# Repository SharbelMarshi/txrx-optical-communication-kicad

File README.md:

# A Free Space Optical Communication
This project implements a free-space optical communication link using two separate KiCad-designed boards: a transmitter and a receiver. The transmitter uses an RP2354A microcontroller to frame arbitrary digital payloads into packets and generate $100 \mathrm{kbit/s}$ RZ-OOK modulation for a $650 \mathrm{nm}$ laser module through a level-shifting buffer and an independent hardware safety chain.
The receiver uses a BPW34 photodiode, OPA320 transimpedance amplifier, and TLV3201 comparator (with an adaptive, average-tracking threshold and hysteresis) to recover the optical pulses and feed them into an RP2354A for decoding, CRC verification, and delivery to the host system.
Both boards include USB-C, UART, SWD, a local $12 \mathrm{MHz}$ crystal, and a $10 \mathrm{MHz}$ SiTime SiT5346 DCTCXO reference. The SiT5346 is connected to the RP2354A through a GPIO/PIO clock input and is controllable over the existing $\text{I²C}$ bus. Each board also exposes a dedicated $1\mathrm{PPS}$ output generated by the RP2354A. The initial target is a stable free-space optical link over approximately $5$ meters.

## Architecture
Two separate $4$ layer boards:
- TX: RP2354A + USB-C + host I/O + $12 \mathrm{MHz}$ crystal + $10 \mathrm{MHz}$ SiT5346 DCTCXO + dedicated $1\mathrm{PPS}$ output + laser driver/safety chain + laser module + power LED + host-5 V TVS protection.
- RX: RP2354A + USB-C + host I/O + $12 \mathrm{MHz}$ crystal + $10 \mathrm{MHz}$ SiT5346 DCTCXO + dedicated $1\mathrm{PPS}$ output + BPW34 / OPA320 / TLV3201 optical receiver + ADC monitor + power LED + host-5 V TVS protection.

### TX
- TX_ROOT
- TX_POWER_USB
- TX_MCU_CLOCK
- TX_HOST_IO
- TX_LASER

### RX
- RX_ROOT
- RX_POWER_USB
- RX_MCU_CLOCK
- RX_HOST_IO
- RX_OPTICAL_AFE
- RX_MONITOR

### TX schamtics:

### TX PCB: 

### RX schamtics:

### RX PCB: 

## Design updates (November 2026)
- **JLCPCB stock swaps:** 12 MHz crystal → YXC X322512MMB4SI; laser arm switch SW3 → C&K JS202011CQN; J2 / TX J4 → Würth 2.54 mm headers; USB-C → HH 16P TYPE-C (Y495); SWD header → FTSH-105-01-F-DV-K.
- **RX optical front end:** TIA gain R15 = 10 kΩ with C28 = 10 pF; adaptive comparator threshold (R13 = 100 kΩ from TIA_OUT, R12 = 2.2 MΩ, C25 = 10 nF); hysteresis via R16 = 1 kΩ and R17 = 470 kΩ.
- **Protection and indicators:** host 5 V input TVS (TX D2 SMF5.0A, RX D3 CESD5V0D3); red power LED on +3V3_DIG (TX R15/D1, RX R19/D2); 10 µF bulk capacitor on the TX 5 V rail (C26).
- **10 MHz reference:** 33 Ω series source termination at each SiT5346 output (TX R14, RX R18; oscillator side net `REF_10M_SRC`).
- **Decoupling:** two extra 100 nF 0402 capacitors on RX (C30 at IOVDD pin 45, C31 at VREG_VIN pin 49). The RP2354A core-supply (DVDD) decoupling still needs a manual fan-out rework, since there is no room near those pins without rerouting.
- **Test points:** RX TP1 = TIA_OUT, TP2 = COMP_THRESHOLD (bottom side), TP3 = RX_DATA_DIG; TX TP1 = LASER_DATA_3V3. Laser power/data and GND are also on the TX J4 header pins.
- **Silkscreen:** bottom-side pin names for J2, JP1 (USB / HOST), J4, J5/J6, test points, and board name/revision. SW3 is marked **ARM** (slider toward the top end, pin 1) and **SAFE**, per the C&K JS circuit diagram; confirm with a meter before first laser use.
- **Panelization:** copper-to-edge clearance raised to 0.4 mm for V-scoring. The RX outline was widened by 2.5 mm on the left (header side, no copper), so both boards are 52.09 × 40.0 mm and V-score lines line up. Panel options (all 2×2, V-scored, 5 mm rails with tooling holes and fiducials):
  - `Manufacturing/TXRX_1x2_panel`: one row, TX left and RX right (about 104.2 × 50.0 mm). One panel gives one TX/RX pair.
  - `Manufacturing/TXRX_panel`: mixed panel, top row 2× TX and bottom row 2× RX (about 104.2 × 90.0 mm). One panel gives two TX/RX pairs.
  - `Manufacturing/TX/panel` and `Manufacturing/RX/panel`: single-design panels, 4 boards each.
- **Manufacturing:** JLCPCB-format BOM and CPL files (single board and panel) are in `Manufacturing/TX` and `Manufacturing/RX`. The SiT5346 is sourced and fitted separately, so it is left out of those files.
- **Optical (not on the PCB):** fit a 650 nm band-pass (or red) filter and a short black tube over the BPW34 to reject ambient light.

## Library:
### Pre-built Components Compatibility Verfication:

Verified: Symbol and Footprint compatibility: 

1. RP2354A  ✓
2. AP2112K-3.3  ✓
3. SN74AHCT1G125DBVR  ✓
4. TPS22919DCKR  ✓
5. USBLC6-2SC6  ✓
7. REF2033  ✓
8. SMF5.0A TVS (Diode_SMD:D_SOD-123F, TX)  ✓
9. CESD5V0D3 TVS (Diode_SMD:D_SOD-323, RX)  ✓
10. KT-0603R red LED (LED_SMD:LED_0603_1608Metric)  ✓

### Costum Components:

1. SiT5346 ✓
2. OPA320  ✓
3. TLV3201 ✓
4. BPW34 (custom footprint)  ✓
5. TPS7A2033  (customed symbol) ✓
6. ABM8-272-T3_3225 (custom footprint), fitted with YXC X322512MMB4SI (12 MHz, 10 pF; replaces ABM8-272-T3)  ✓
7. AOTA-B201610S3R3-101-T (custom footprint) ✓
8. SW_CK_JS202011CQN_as_DPST (custom footprint) for C&K JS202011CQN slide switch (replaces ES22MCBE) ✓
9. Würth 61300311121, 1×3 2.54 mm header (replaces B3B-PH-K-S) ✓
10. Würth 61300811121, 1×8 2.54 mm header (replaces B8B-PH-K-S) ✓
11. ARD-LASER-MDI650-1-5 ✓
12. FTSH-105-01-F-DV-K (replaces FTSH-105-01-L-DV-K, same footprint) ✓
13. HH 16P TYPE-C (Y495), LCSC C52209111 (replaces USB4105-GF-A) ✓

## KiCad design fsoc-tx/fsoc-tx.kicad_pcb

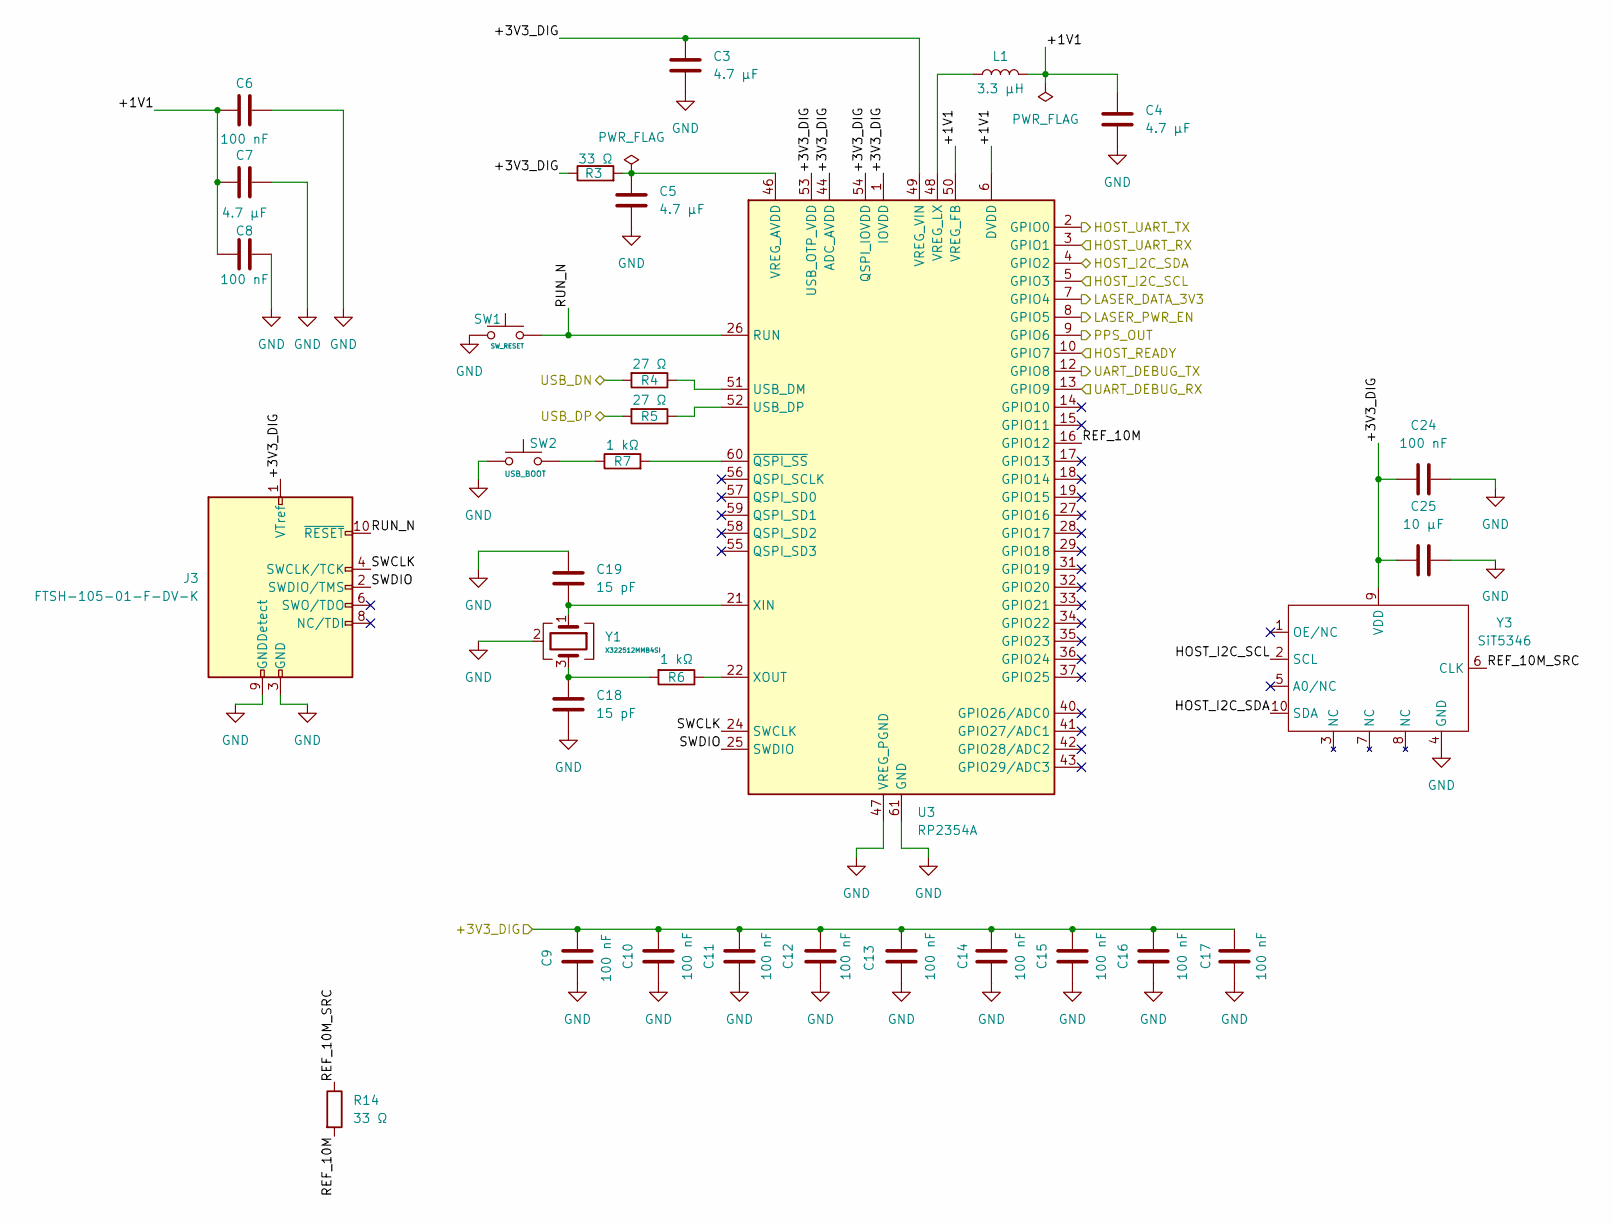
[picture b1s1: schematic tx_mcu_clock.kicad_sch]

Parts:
C3, C4, C5, C7: 4.7 µF; C_0805_2012Metric; MPN CL21A475KAQNNNE; JLCPCB Part C1779
C6, C8, C9, C10, C11, C12, C13, C14, C15, C16, C17, C24: 100 nF; C_0603_1608Metric; MPN CC0603KRX7R9BB104; JLCPCB Part C14663
C18, C19: 15 pF; C_0603_1608Metric; MPN CL10C150JB8NNNC; JLCPCB Part C1644
C25: 10 µF; C_0805_2012Metric; MPN CL21A106KAYNNNE; JLCPCB Part C15850
J3: FTSH-105-01-F-DV-K; FTSH-105-01-L-DV-K; MPN FTSH-105-01-F-DV-K; JLCPCB Part C5382952
L1: 3.3 µH; AOTA-B201610S3R3-101-T; MPN AOTA-B201610S3R3-101-T; JLCPCB Part C42411119
R3, R14: 33 Ω; R_0603_1608Metric; MPN 0603WAF330JT5E; JLCPCB Part C23140
R4, R5: 27 Ω; R_0603_1608Metric; MPN 0603WAF270JT5E; JLCPCB Part C25190
R6, R7: 1 kΩ; R_0603_1608Metric; MPN 0603WAF1001T5E; JLCPCB Part C21190
SW1: SW_RESET; SW_SPST_PTS645Sx43SMTR92; MPN PTS645SM43SMTR92 LFS; JLCPCB Part C221880
SW2: USB_BOOT; SW_SPST_PTS645Sx43SMTR92; MPN PTS645SM43SMTR92 LFS; JLCPCB Part C221880
U3: RP2354A; RP2354A_ThermalVia_0p30; MPN RP2354A; JLCPCB Part C41378174
Y1: X322512MMB4SI; ABM8-272-T3_3225; MPN X322512MMB4SI; JLCPCB Part C50430
Y3: SiT5346; SiT5346_5.0x3.2mm_10L; MPN TBD - SiT5346 10MHz 3.3V LVCMOS DCTCXO; JLCPCB Part TBD - Global Sourcing if not stocked

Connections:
/+3V3_DIG: C3.1, C9.2, C10.2, C11.2, C12.2, C13.2, C14.2, C15.2, C16.2, C17.2, C24.1, C25.1, J3.1 (VTref), R3.1, U3.1 (IOVDD), U3.11 (IOVDD), U3.20 (IOVDD), U3.30 (IOVDD), U3.38 (IOVDD), U3.44 (ADC_AVDD), U3.45 (IOVDD), U3.49 (VREG_VIN), U3.53 (USB_OTP_VDD), U3.54 (QSPI_IOVDD), Y3.9 (VDD); also elsewhere on the board
/HOST_I2C_SCL: U3.5 (GPIO3), Y3.2 (SCL); also elsewhere on the board
/HOST_I2C_SDA: U3.4 (GPIO2), Y3.10 (SDA); also elsewhere on the board
/HOST_READY: U3.10 (GPIO7); also elsewhere on the board
/HOST_UART_RX: U3.3 (GPIO1); also elsewhere on the board
/HOST_UART_TX: U3.2 (GPIO0); also elsewhere on the board
/LASER_DATA_3V3: U3.7 (GPIO4); also elsewhere on the board
/LASER_PWR_EN: U3.8 (GPIO5); also elsewhere on the board
/PPS_OUT: U3.9 (GPIO6); also elsewhere on the board
/TX_MCU_CLOCK/+1V1: C4.1, C6.1, C7.1, C8.2, L1.2, U3.6 (DVDD), U3.23 (DVDD), U3.39 (DVDD), U3.50 (VREG_FB)
/TX_MCU_CLOCK/REF_10M: R14.2, U3.16 (GPIO12)
/TX_MCU_CLOCK/REF_10M_SRC: R14.1, Y3.6 (CLK)
/TX_MCU_CLOCK/RUN_N: J3.10 (~RESET), SW1.1, U3.26 (RUN)
/TX_MCU_CLOCK/SWCLK: J3.4 (SWCLK/TCK), U3.24 (SWCLK)
/TX_MCU_CLOCK/SWDIO: J3.2 (SWDIO/TMS), U3.25 (SWDIO)
/UART_DEBUG_RX: U3.13 (GPIO9); also elsewhere on the board
/UART_DEBUG_TX: U3.12 (GPIO8); also elsewhere on the board
/USB_DN: R4.2; also elsewhere on the board
/USB_DP: R5.2; also elsewhere on the board
GND: C3.2, C4.2, C5.2, C6.2, C7.2, C8.1, C9.1, C10.1, C11.1, C12.1, C13.1, C14.1, C15.1, C16.1, C17.1, C18.2, C19.1, C24.2, C25.2, J3.3 (GND), J3.5 (GND), J3.9 (GNDDetect), SW1.2, SW2.1, U3.47 (VREG_PGND), U3.61 (GND), Y1.2 (G), Y1.4 (G), Y3.4 (GND); also elsewhere on the board
unnamed: C18.1, R6.2, Y1.3
unnamed: R7.1, SW2.2
unnamed: R4.1, U3.51 (USB_DM)
unnamed: R5.1, U3.52 (USB_DP)
unnamed: C5.1, R3.2, U3.46 (VREG_AVDD)
unnamed: L1.1, U3.48 (VREG_LX)
unnamed: C19.2, U3.21 (XIN), Y1.1
unnamed: R6.1, U3.22 (XOUT)
unnamed: R7.2, U3.60 (~QSPI_SS)

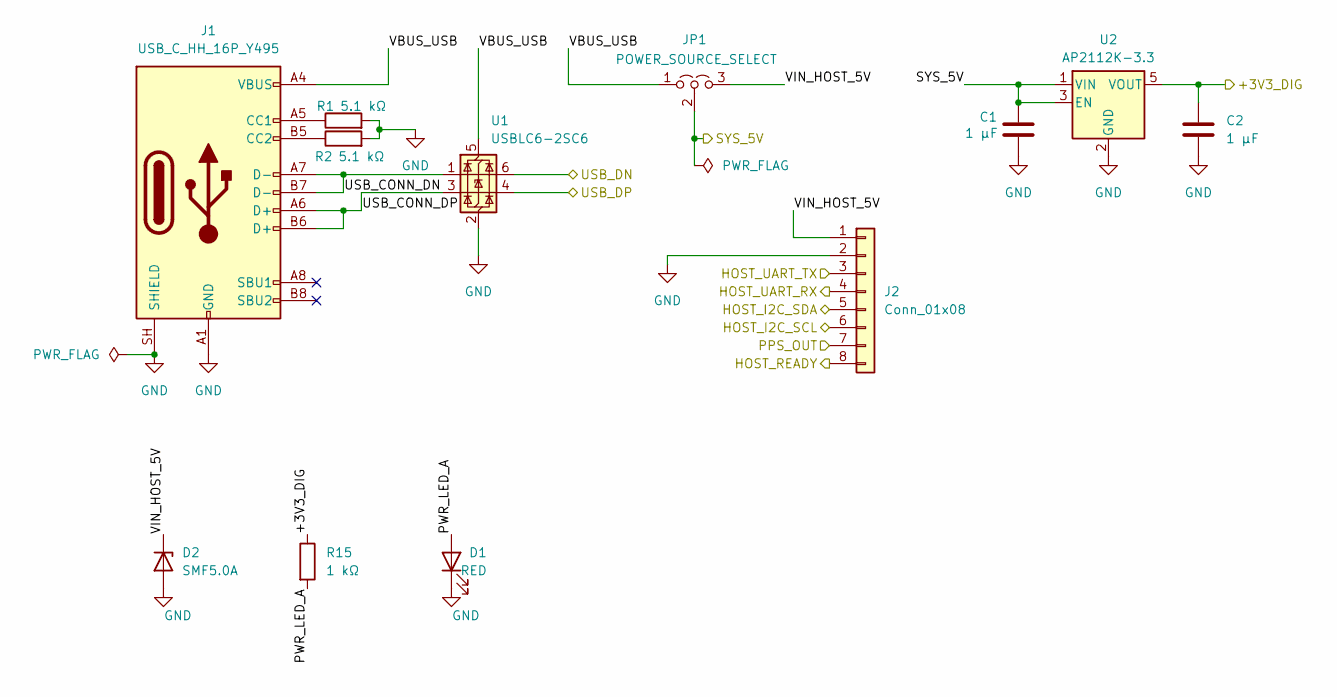
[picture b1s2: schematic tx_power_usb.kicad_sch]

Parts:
C1, C2: 1 µF; C_0805_2012Metric; MPN CL21B105KBFNNNE; JLCPCB Part C28323
D1: RED; LED_0603_1608Metric; MPN KT-0603R; JLCPCB Part C2286
D2: SMF5.0A; D_SOD-123F; MPN SMF5.0A; JLCPCB Part C193402
J1: USB_C_HH_16P_Y495; MPN HH 16P TYPE-C (Y495); JLCPCB Part C52209111
J2: Conn_01x08; PinHeader_1x08_P2.54mm_Vertical; MPN 61300811121; JLCPCB Part C6400764
JP1: POWER_SOURCE_SELECT; PinHeader_1x03_P2.54mm_Vertical; MPN 61300311121; JLCPCB Part C2915006
R1, R2: 5.1 kΩ; R_0603_1608Metric; MPN 0603WAF5101T5E; JLCPCB Part C23186
R15: 1 kΩ; R_0603_1608Metric; MPN 0603WAF1001T5E; JLCPCB Part C21190
U1: USBLC6-2SC6; SOT-23-6; MPN USBLC6-2SC6; JLCPCB Part C7519
U2: AP2112K-3.3; SOT-23-5; MPN AP2112K-3.3TRG1; JLCPCB Part C51118

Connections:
/+3V3_DIG: C2.1, R15.1, U2.5 (VOUT); also elsewhere on the board
/HOST_I2C_SCL: J2.6; also elsewhere on the board
/HOST_I2C_SDA: J2.5; also elsewhere on the board
/HOST_READY: J2.8; also elsewhere on the board
/HOST_UART_RX: J2.4; also elsewhere on the board
/HOST_UART_TX: J2.3; also elsewhere on the board
/PPS_OUT: J2.7; also elsewhere on the board
/SYS_5V: C1.1, JP1.2 (C), U2.1 (VIN), U2.3 (EN); also elsewhere on the board
/TX_POWER_USB/PWR_LED_A: D1.2 (A), R15.2
/TX_POWER_USB/USB_CONN_DN: J1.A7 (D-), J1.B7 (D-), U1.1 (I/O1)
/TX_POWER_USB/USB_CONN_DP: J1.A6 (D+), J1.B6 (D+), U1.3 (I/O2)
/TX_POWER_USB/VBUS_USB: J1.A4 (VBUS), J1.A9 (VBUS), J1.B4 (VBUS), J1.B9 (VBUS), JP1.1 (A), U1.5 (VBUS)
/TX_POWER_USB/VIN_HOST_5V: D2.1 (K), J2.1, JP1.3 (B)
/USB_DN: U1.6 (I/O1); also elsewhere on the board
/USB_DP: U1.4 (I/O2); also elsewhere on the board
GND: C1.2, C2.2, D1.1 (K), D2.2 (A), J1.A1 (GND), J1.A12 (GND), J1.B1 (GND), J1.B12 (GND), J1.SH (SHIELD), J2.2, R1.2, R2.2, U1.2 (GND), U2.2 (GND); also elsewhere on the board
unnamed: J1.A5 (CC1), R1.1
unnamed: J1.B5 (CC2), R2.1

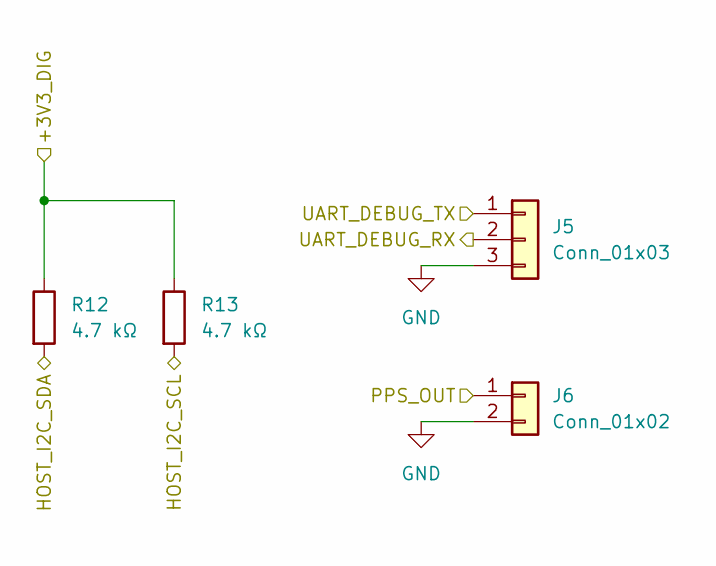
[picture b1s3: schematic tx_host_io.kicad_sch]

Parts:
J5: Conn_01x03; PinHeader_1x03_P2.54mm_Vertical; MPN 61300311121; JLCPCB Part C2915006
J6: Conn_01x02; PinHeader_1x02_P2.54mm_Vertical; MPN 61300211121; JLCPCB Part C2915055
R12, R13: 4.7 kΩ; R_0603_1608Metric; MPN 0603WAF4701T5E; JLCPCB Part C23162

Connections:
/+3V3_DIG: R12.1, R13.1; also elsewhere on the board
/HOST_I2C_SCL: R13.2; also elsewhere on the board
/HOST_I2C_SDA: R12.2; also elsewhere on the board
/PPS_OUT: J6.1; also elsewhere on the board
/UART_DEBUG_RX: J5.2; also elsewhere on the board
/UART_DEBUG_TX: J5.1; also elsewhere on the board
GND: J5.3, J6.2; also elsewhere on the board

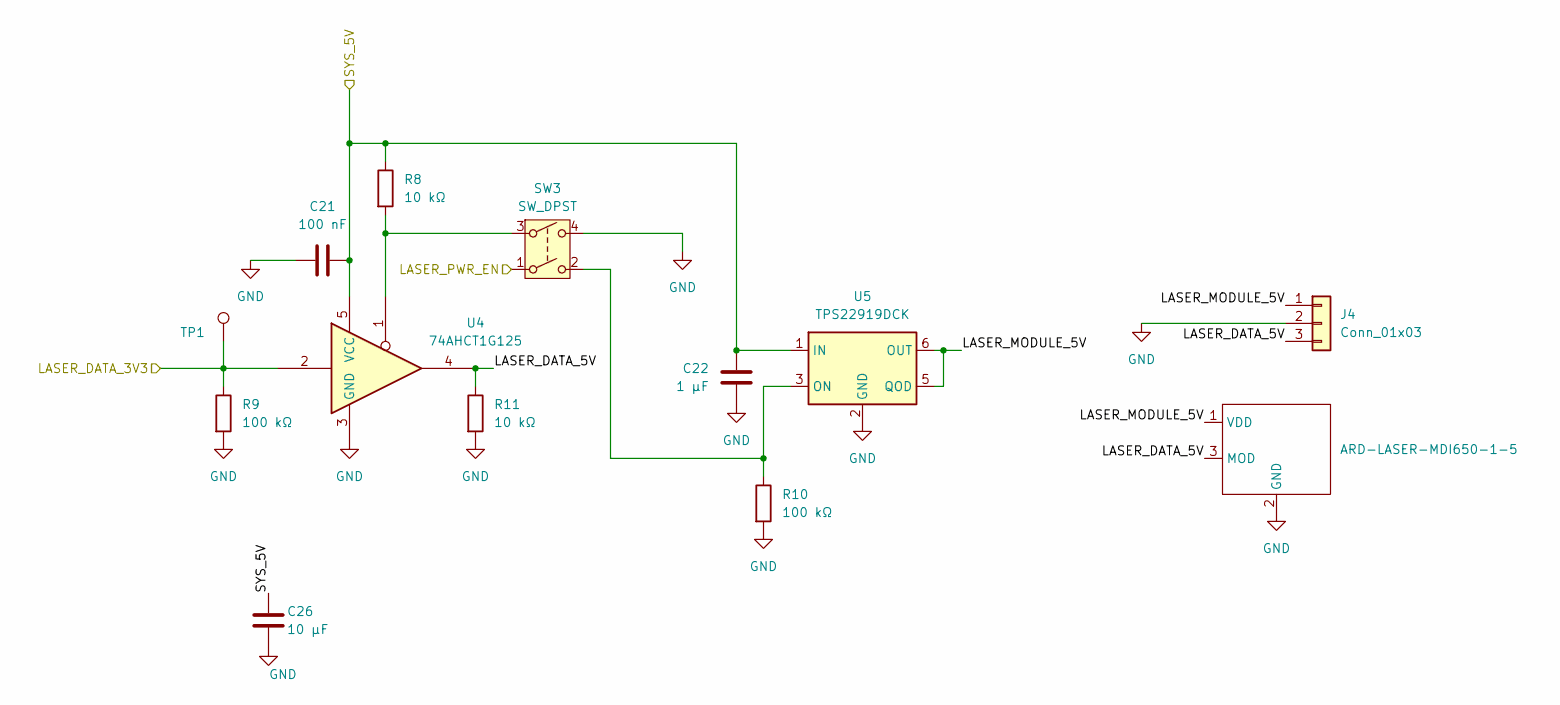
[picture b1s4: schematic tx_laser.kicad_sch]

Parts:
C21: 100 nF; C_0603_1608Metric; MPN CC0603KRX7R9BB104; JLCPCB Part C14663
C22: 1 µF; C_0805_2012Metric; MPN CL21B105KBFNNNE; JLCPCB Part C28323
C26: 10 µF; C_0805_2012Metric; MPN CL21A106KAYNNNE; JLCPCB Part C15850
J4: Conn_01x03; PinHeader_1x03_P2.54mm_Vertical; MPN 61300311121; JLCPCB Part C2915006
MOD1: ARD-LASER-MDI650-1-5; MPN ARD-LASER-MDI650-1-5(10x26)
R8, R11: 10 kΩ; R_0603_1608Metric; MPN 0603WAF1002T5E; JLCPCB Part C25804
R9, R10: 100 kΩ; R_0603_1608Metric; MPN 0603WAF1003T5E; JLCPCB Part C25803
SW3: SW_DPST; SW_CK_JS202011CQN_as_DPST; MPN JS202011CQN; JLCPCB Part C221663
TP1: LASER_DATA_3V3; TestPoint_Pad_D1.0mm
U4: 74AHCT1G125; SOT-23-5; MPN SN74AHCT1G125DBVR; JLCPCB Part C7484
U5: TPS22919DCK; SOT-363_SC-70-6; MPN TPS22919DCKR; JLCPCB Part C2149796

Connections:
/LASER_DATA_3V3: R9.1, TP1.1, U4.2; also elsewhere on the board
/LASER_PWR_EN: SW3.1; also elsewhere on the board
/SYS_5V: C21.2, C22.1, C26.1, R8.1, U4.5 (VCC), U5.1 (IN); also elsewhere on the board
/TX_LASER/LASER_DATA_5V: J4.3, MOD1.3 (MOD), R11.1, U4.4
/TX_LASER/LASER_MODULE_5V: J4.1, MOD1.1 (VDD), U5.5 (QOD), U5.6 (OUT)
GND: C21.1, C22.2, C26.2, J4.2, MOD1.2 (GND), R9.2, R10.2, R11.2, SW3.4, U4.3 (GND), U5.2 (GND); also elsewhere on the board
unnamed: R8.2, SW3.3, U4.1
unnamed: R10.1, SW3.2, U5.3 (ON)

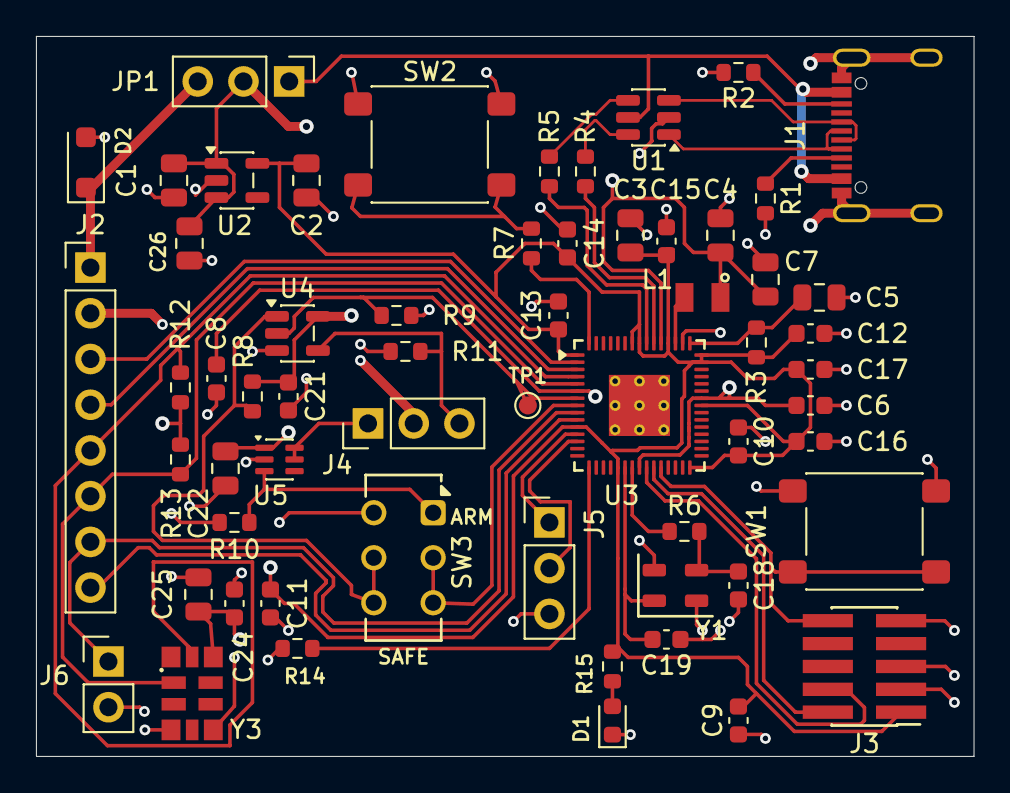
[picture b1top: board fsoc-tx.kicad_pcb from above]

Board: 4 copper layers, 52.1 x 40.0 mm, 60 parts (0 on the bottom side), 41 nets.

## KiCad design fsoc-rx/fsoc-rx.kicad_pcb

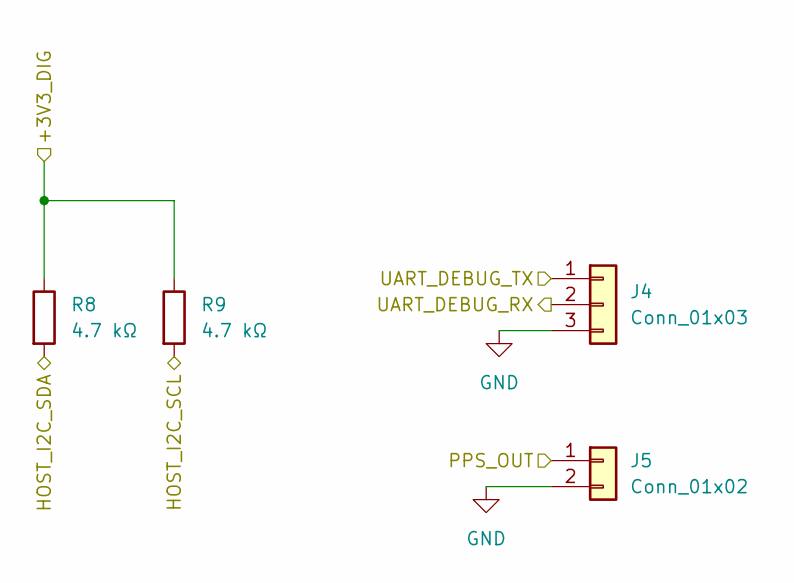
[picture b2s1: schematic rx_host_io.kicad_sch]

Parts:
J4: Conn_01x03; PinHeader_1x03_P2.54mm_Vertical; MPN 61300311121; JLCPCB Part C2915006
J5: Conn_01x02; PinHeader_1x02_P2.54mm_Vertical; MPN 61300211121; JLCPCB Part C2915055
R8, R9: 4.7 kΩ; R_0603_1608Metric; MPN 0603WAF4701T5E; JLCPCB Part C23162

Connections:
/+3V3_DIG: R8.1, R9.1; also elsewhere on the board
/HOST_I2C_SCL: R9.2; also elsewhere on the board
/HOST_I2C_SDA: R8.2; also elsewhere on the board
/PPS_OUT: J5.1; also elsewhere on the board
/UART_DEBUG_RX: J4.2; also elsewhere on the board
/UART_DEBUG_TX: J4.1; also elsewhere on the board
GND: J4.3, J5.2; also elsewhere on the board

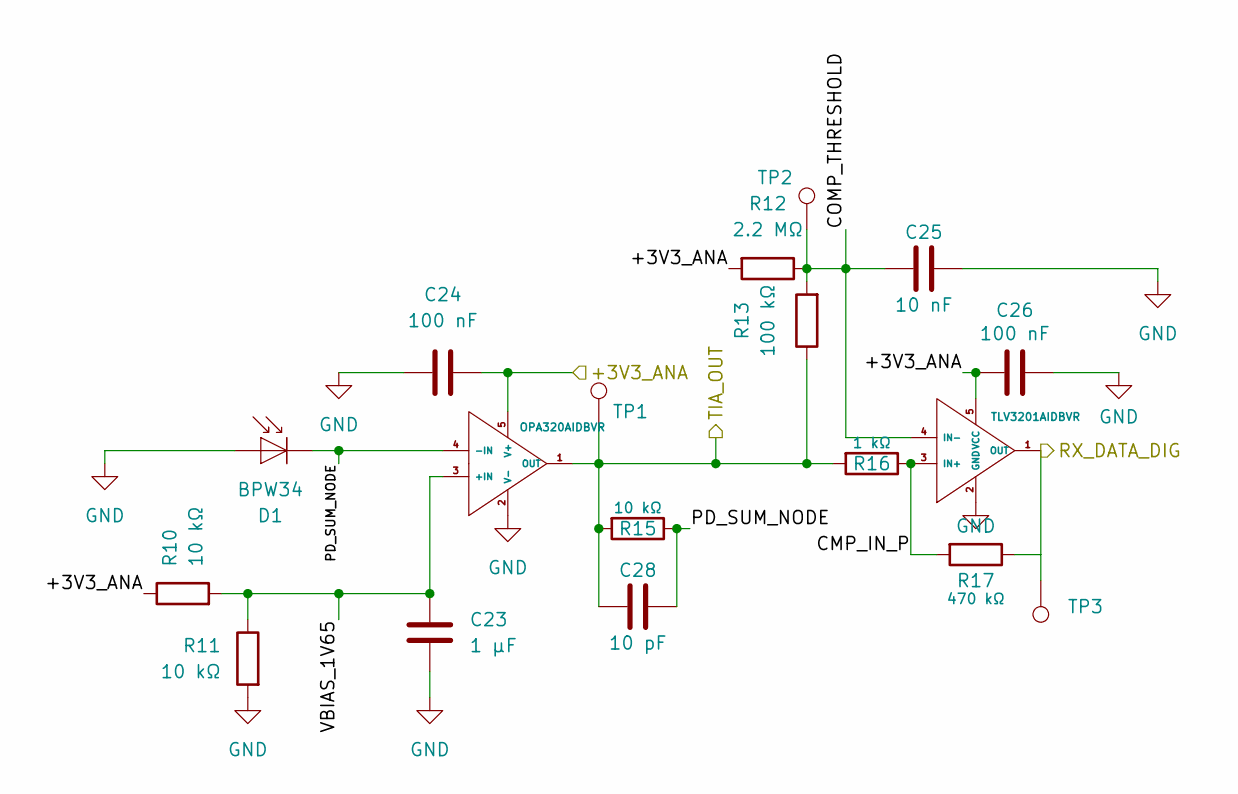
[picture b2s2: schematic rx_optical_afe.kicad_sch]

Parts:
C23: 1 µF; C_0805_2012Metric; MPN CL21B105KBFNNNE; JLCPCB Part C28323
C24, C26: 100 nF; C_0603_1608Metric; MPN CC0603KRX7R9BB104; JLCPCB Part C14663
C25: 10 nF; C_0603_1608Metric; MPN 0603B103K500NT; JLCPCB Part C57112
C28: 10 pF; C_0603_1608Metric; MPN CL10C100JB8NNNC; JLCPCB Part C1634
D1: BPW34; BPW34_Vishay; MPN BPW34; JLCPCB Part C85128
R10, R11, R15: 10 kΩ; R_0603_1608Metric; MPN 0603WAF1002T5E; JLCPCB Part C25804
R12: 2.2 MΩ; R_0603_1608Metric; MPN 0603WAF2204T5E; JLCPCB Part C22938
R13: 100 kΩ; R_0603_1608Metric; MPN 0603WAF1003T5E; JLCPCB Part C25803
R16: 1 kΩ; R_0603_1608Metric; MPN 0603WAF1001T5E; JLCPCB Part C21190
R17: 470 kΩ; R_0402_1005Metric; MPN 0402WGF4703TCE; JLCPCB Part C25790
TP1: TIA_OUT; TestPoint_Pad_D1.0mm
TP2: COMP_THRESHOLD; TestPoint_Pad_D1.5mm
TP3: RX_DATA_DIG; TestPoint_Pad_D1.0mm
U5: OPA320AIDBVR; SOT-23-5; MPN OPA320AIDBVR; JLCPCB Part C92494
U6: TLV3201AIDBVR; SOT-23-5; MPN TLV3201AIDBVR; JLCPCB Part C105188

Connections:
/+3V3_ANA: C24.2, C26.2, R10.1, R12.2, U5.5 (V+), U6.5 (VCC); also elsewhere on the board
/RX_DATA_DIG: R17.1, TP3.1, U6.1 (OUT); also elsewhere on the board
/RX_OPTICAL_AFE/CMP_IN_P: R16.1, R17.2, U6.3 (IN+)
/RX_OPTICAL_AFE/COMP_THRESHOLD: C25.1, R12.1, R13.2, TP2.1, U6.4 (IN-)
/RX_OPTICAL_AFE/PD_SUM_NODE: C28.2, D1.1 (K), R15.1, U5.4 (-IN)
/RX_OPTICAL_AFE/VBIAS_1V65: C23.1, R10.2, R11.1, U5.3 (+IN)
/TIA_OUT: C28.1, R13.1, R15.2, R16.2, TP1.1, U5.1 (OUT); also elsewhere on the board
GND: C23.2, C24.1, C25.2, C26.1, D1.2 (A), R11.2, U5.2 (V-), U6.2 (GND); also elsewhere on the board

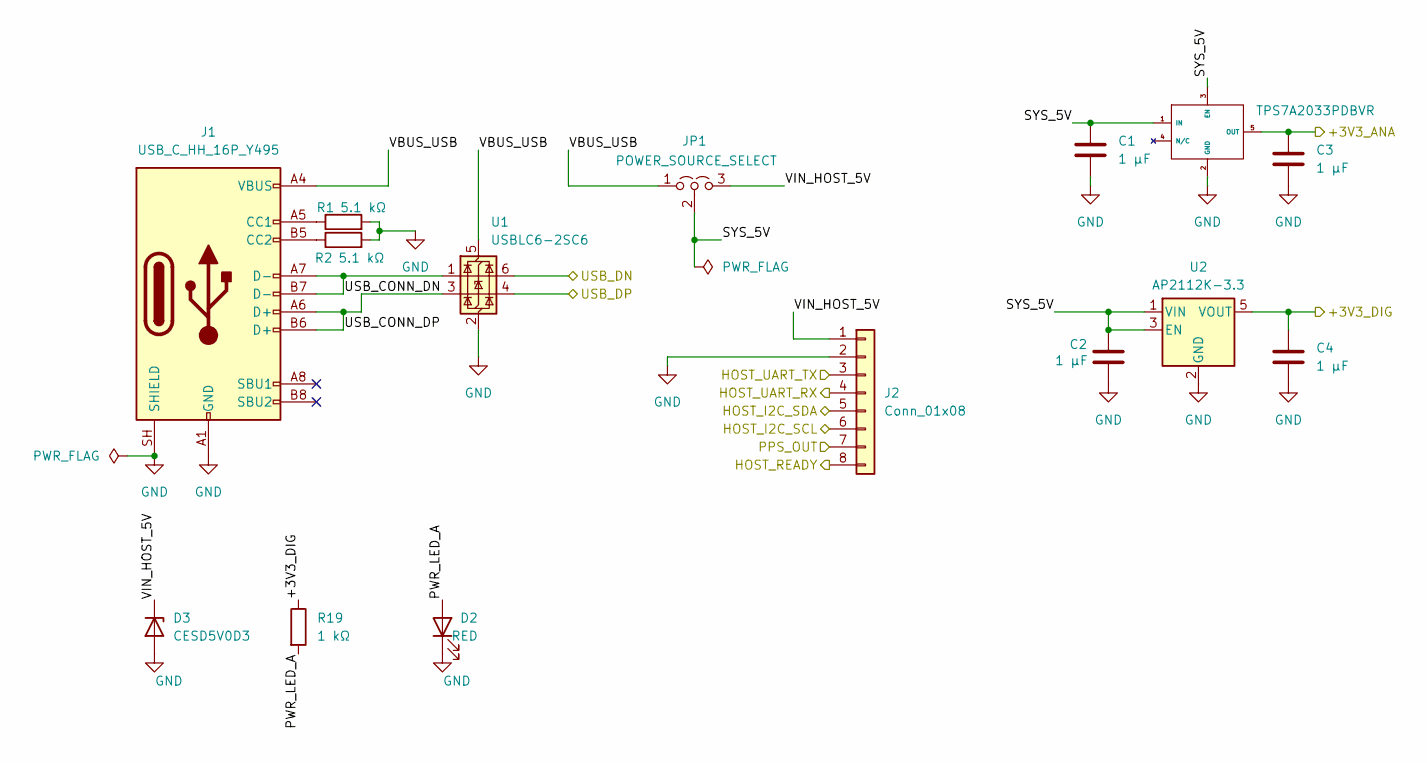
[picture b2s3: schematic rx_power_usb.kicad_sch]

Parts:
C1, C2, C3, C4: 1 µF; C_0805_2012Metric; MPN CL21B105KBFNNNE; JLCPCB Part C28323
D2: RED; LED_0603_1608Metric; MPN KT-0603R; JLCPCB Part C2286
D3: CESD5V0D3; D_SOD-323; MPN CESD5V0D3; JLCPCB Part C19829531
J1: USB_C_HH_16P_Y495; MPN HH 16P TYPE-C (Y495); JLCPCB Part C52209111
J2: Conn_01x08; PinHeader_1x08_P2.54mm_Vertical; MPN 61300811121; JLCPCB Part C6400764
JP1: POWER_SOURCE_SELECT; PinHeader_1x03_P2.54mm_Vertical; MPN 61300311121; JLCPCB Part C2915006
R1, R2: 5.1 kΩ; R_0603_1608Metric; MPN 0603WAF5101T5E; JLCPCB Part C23186
R19: 1 kΩ; R_0603_1608Metric; MPN 0603WAF1001T5E; JLCPCB Part C21190
U1: USBLC6-2SC6; SOT-23-6; MPN USBLC6-2SC6; JLCPCB Part C7519
U2: AP2112K-3.3; SOT-23-5; MPN AP2112K-3.3TRG1; JLCPCB Part C51118
U3: TPS7A2033PDBVR; SOT-23-5; MPN TPS7A2033PDBVR; JLCPCB Part C2862740

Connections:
/+3V3_ANA: C3.1, U3.5 (OUT); also elsewhere on the board
/+3V3_DIG: C4.1, R19.1, U2.5 (VOUT); also elsewhere on the board
/HOST_I2C_SCL: J2.6; also elsewhere on the board
/HOST_I2C_SDA: J2.5; also elsewhere on the board
/HOST_READY: J2.8; also elsewhere on the board
/HOST_UART_RX: J2.4; also elsewhere on the board
/HOST_UART_TX: J2.3; also elsewhere on the board
/PPS_OUT: J2.7; also elsewhere on the board
/RX_POWER_USB/PWR_LED_A: D2.2 (A), R19.2
/RX_POWER_USB/SYS_5V: C1.1, C2.1, JP1.2 (C), U2.1 (VIN), U2.3 (EN), U3.1 (IN), U3.3 (EN)
/RX_POWER_USB/USB_CONN_DN: J1.A7 (D-), J1.B7 (D-), U1.1 (I/O1)
/RX_POWER_USB/USB_CONN_DP: J1.A6 (D+), J1.B6 (D+), U1.3 (I/O2)
/RX_POWER_USB/VBUS_USB: J1.A4 (VBUS), J1.A9 (VBUS), J1.B4 (VBUS), J1.B9 (VBUS), JP1.1 (A), U1.5 (VBUS)
/RX_POWER_USB/VIN_HOST_5V: D3.1 (K), J2.1, JP1.3 (B)
/USB_DN: U1.6 (I/O1); also elsewhere on the board
/USB_DP: U1.4 (I/O2); also elsewhere on the board
GND: C1.2, C2.2, C3.2, C4.2, D2.1 (K), D3.2 (A), J1.A1 (GND), J1.A12 (GND), J1.B1 (GND), J1.B12 (GND), J1.SH (SHIELD), J2.2, R1.2, R2.2, U1.2 (GND), U2.2 (GND), U3.2 (GND); also elsewhere on the board
unnamed: J1.A5 (CC1), R1.1
unnamed: J1.B5 (CC2), R2.1

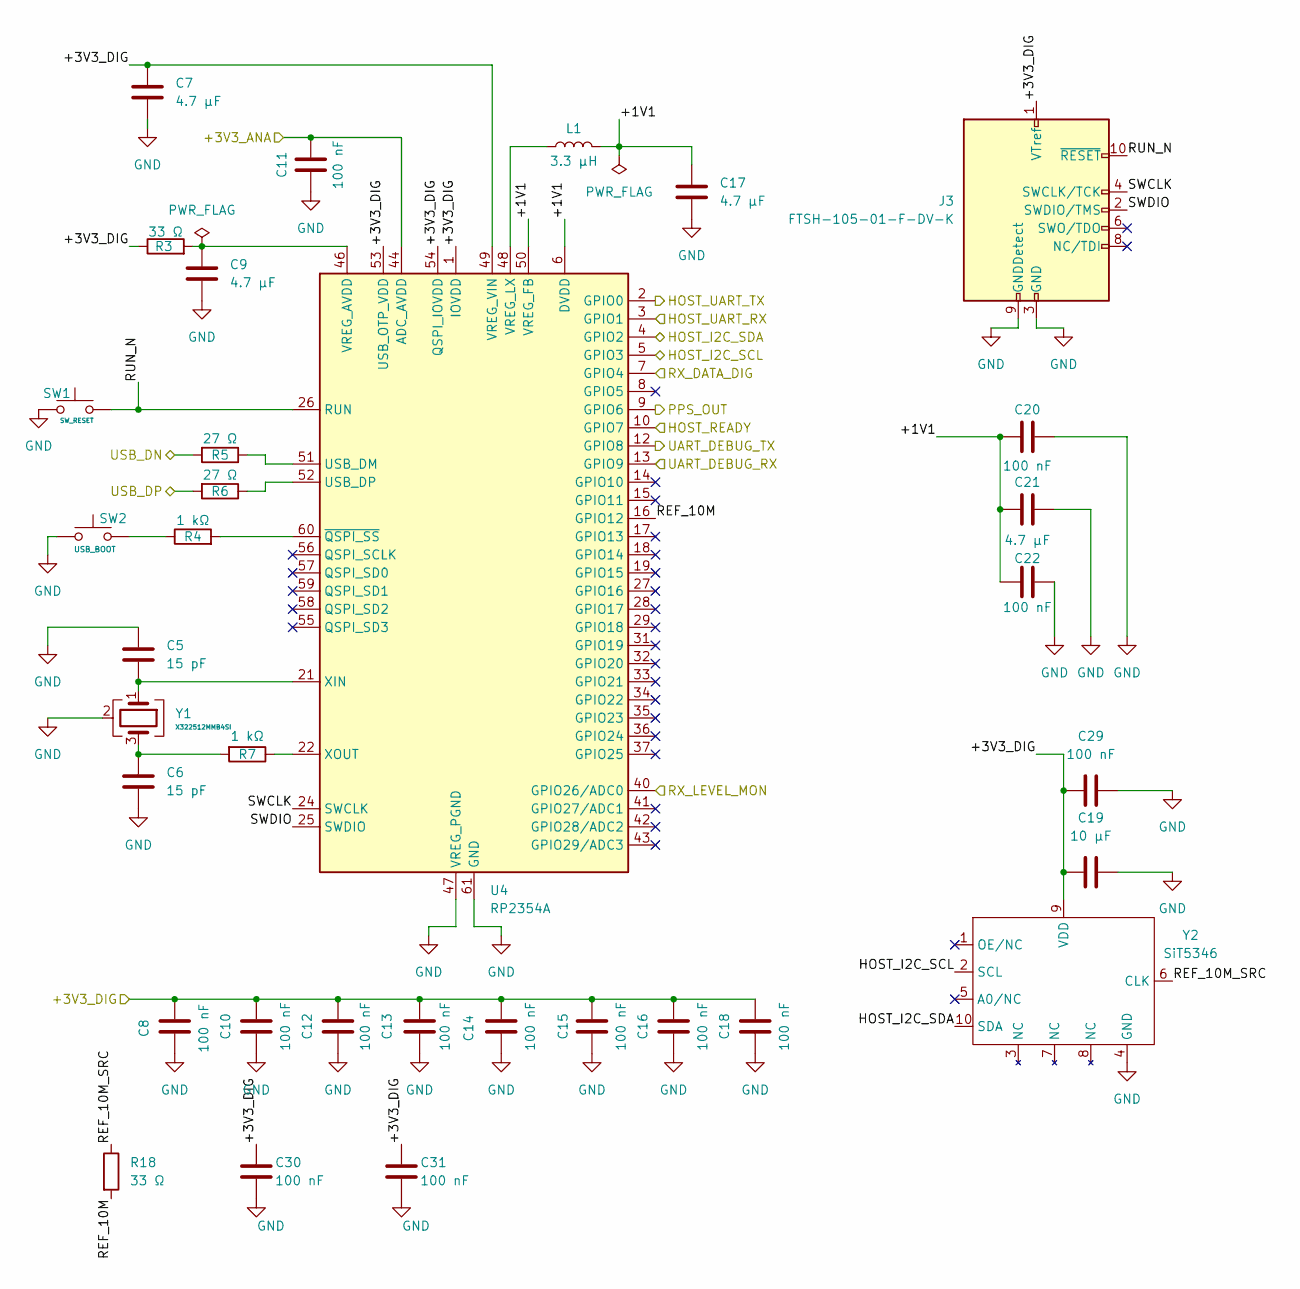
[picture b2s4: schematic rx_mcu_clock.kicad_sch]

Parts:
C5, C6: 15 pF; C_0603_1608Metric; MPN CL10C150JB8NNNC; JLCPCB Part C1644
C7, C9, C17, C21: 4.7 µF; C_0805_2012Metric; MPN CL21A475KAQNNNE; JLCPCB Part C1779
C8, C10, C11, C12, C13, C14, C15, C16, C18, C20, C22, C29: 100 nF; C_0603_1608Metric; MPN CC0603KRX7R9BB104; JLCPCB Part C14663
C19: 10 µF; C_0805_2012Metric; MPN CL21A106KAYNNNE; JLCPCB Part C15850
C30, C31: 100 nF; C_0402_1005Metric; MPN CL05B104KO5NNNC; JLCPCB Part C1525
J3: FTSH-105-01-F-DV-K; FTSH-105-01-L-DV-K; MPN FTSH-105-01-F-DV-K; JLCPCB Part C5382952
L1: 3.3 µH; AOTA-B201610S3R3-101-T; MPN AOTA-B201610S3R3-101-T; JLCPCB Part C42411119
R3, R18: 33 Ω; R_0603_1608Metric; MPN 0603WAF330JT5E; JLCPCB Part C23140
R4, R7: 1 kΩ; R_0603_1608Metric; MPN 0603WAF1001T5E; JLCPCB Part C21190
R5, R6: 27 Ω; R_0603_1608Metric; MPN 0603WAF270JT5E; JLCPCB Part C25190
SW1: SW_RESET; SW_SPST_PTS645Sx43SMTR92; MPN PTS645SM43SMTR92 LFS; JLCPCB Part C221880
SW2: USB_BOOT; SW_SPST_PTS645Sx43SMTR92; MPN PTS645SM43SMTR92 LFS; JLCPCB Part C221880
U4: RP2354A; RP2354A_ThermalVia_0p30; MPN RP2354A; JLCPCB Part C41378174
Y1: X322512MMB4SI; ABM8-272-T3_3225; MPN X322512MMB4SI; JLCPCB Part C50430
Y2: SiT5346; SiT5346_5.0x3.2mm_10L; MPN TBD - SiT5346 10MHz 3.3V LVCMOS DCTCXO; JLCPCB Part TBD - Global Sourcing if not stocked

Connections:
/+3V3_ANA: C11.2, U4.44 (ADC_AVDD); also elsewhere on the board
/+3V3_DIG: C7.1, C8.2, C10.2, C12.2, C13.2, C14.2, C15.2, C16.2, C18.2, C19.1, C29.1, C30.1, C31.1, J3.1 (VTref), R3.1, U4.1 (IOVDD), U4.11 (IOVDD), U4.20 (IOVDD), U4.30 (IOVDD), U4.38 (IOVDD), U4.45 (IOVDD), U4.49 (VREG_VIN), U4.53 (USB_OTP_VDD), U4.54 (QSPI_IOVDD), Y2.9 (VDD); also elsewhere on the board
/HOST_I2C_SCL: U4.5 (GPIO3), Y2.2 (SCL); also elsewhere on the board
/HOST_I2C_SDA: U4.4 (GPIO2), Y2.10 (SDA); also elsewhere on the board
/HOST_READY: U4.10 (GPIO7); also elsewhere on the board
/HOST_UART_RX: U4.3 (GPIO1); also elsewhere on the board
/HOST_UART_TX: U4.2 (GPIO0); also elsewhere on the board
/PPS_OUT: U4.9 (GPIO6); also elsewhere on the board
/RX_DATA_DIG: U4.7 (GPIO4); also elsewhere on the board
/RX_LEVEL_MON: U4.40 (GPIO26/ADC0); also elsewhere on the board
/RX_MCU_CLOCK/+1V1: C17.1, C20.1, C21.1, C22.2, L1.2, U4.6 (DVDD), U4.23 (DVDD), U4.39 (DVDD), U4.50 (VREG_FB)
/RX_MCU_CLOCK/REF_10M: R18.2, U4.16 (GPIO12)
/RX_MCU_CLOCK/REF_10M_SRC: R18.1, Y2.6 (CLK)
/RX_MCU_CLOCK/RUN_N: J3.10 (~RESET), SW1.1, U4.26 (RUN)
/RX_MCU_CLOCK/SWCLK: J3.4 (SWCLK/TCK), U4.24 (SWCLK)
/RX_MCU_CLOCK/SWDIO: J3.2 (SWDIO/TMS), U4.25 (SWDIO)
/UART_DEBUG_RX: U4.13 (GPIO9); also elsewhere on the board
/UART_DEBUG_TX: U4.12 (GPIO8); also elsewhere on the board
/USB_DN: R5.2; also elsewhere on the board
/USB_DP: R6.2; also elsewhere on the board
GND: C5.1, C6.2, C7.2, C8.1, C9.2, C10.1, C11.1, C12.1, C13.1, C14.1, C15.1, C16.1, C17.2, C18.1, C19.2, C20.2, C21.2, C22.1, C29.2, C30.2, C31.2, J3.3 (GND), J3.5 (GND), J3.9 (GNDDetect), SW1.2, SW2.1, U4.47 (VREG_PGND), U4.61 (GND), Y1.2 (G), Y1.4 (G), Y2.4 (GND); also elsewhere on the board
unnamed: C6.1, R7.2, Y1.3
unnamed: R4.1, SW2.2
unnamed: R5.1, U4.51 (USB_DM)
unnamed: R6.1, U4.52 (USB_DP)
unnamed: C9.1, R3.2, U4.46 (VREG_AVDD)
unnamed: L1.1, U4.48 (VREG_LX)
unnamed: C5.2, U4.21 (XIN), Y1.1
unnamed: R7.1, U4.22 (XOUT)
unnamed: R4.2, U4.60 (~QSPI_SS)

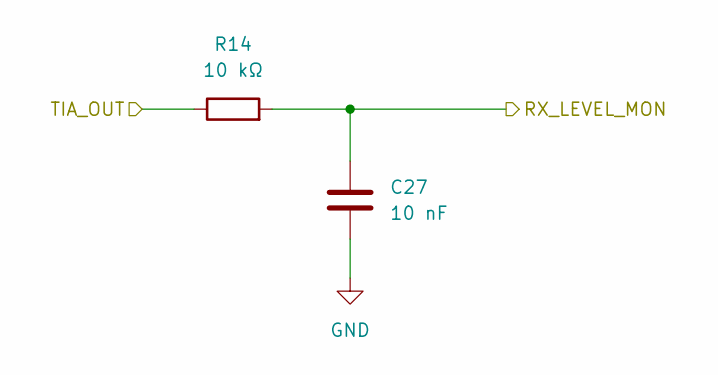
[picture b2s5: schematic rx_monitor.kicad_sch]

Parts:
C27: 10 nF; C_0603_1608Metric; MPN 0603B103K500NT; JLCPCB Part C57112
R14: 10 kΩ; R_0603_1608Metric; MPN 0603WAF1002T5E; JLCPCB Part C25804

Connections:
/RX_LEVEL_MON: C27.1, R14.2; also elsewhere on the board
/TIA_OUT: R14.1; also elsewhere on the board
GND: C27.2; also elsewhere on the board

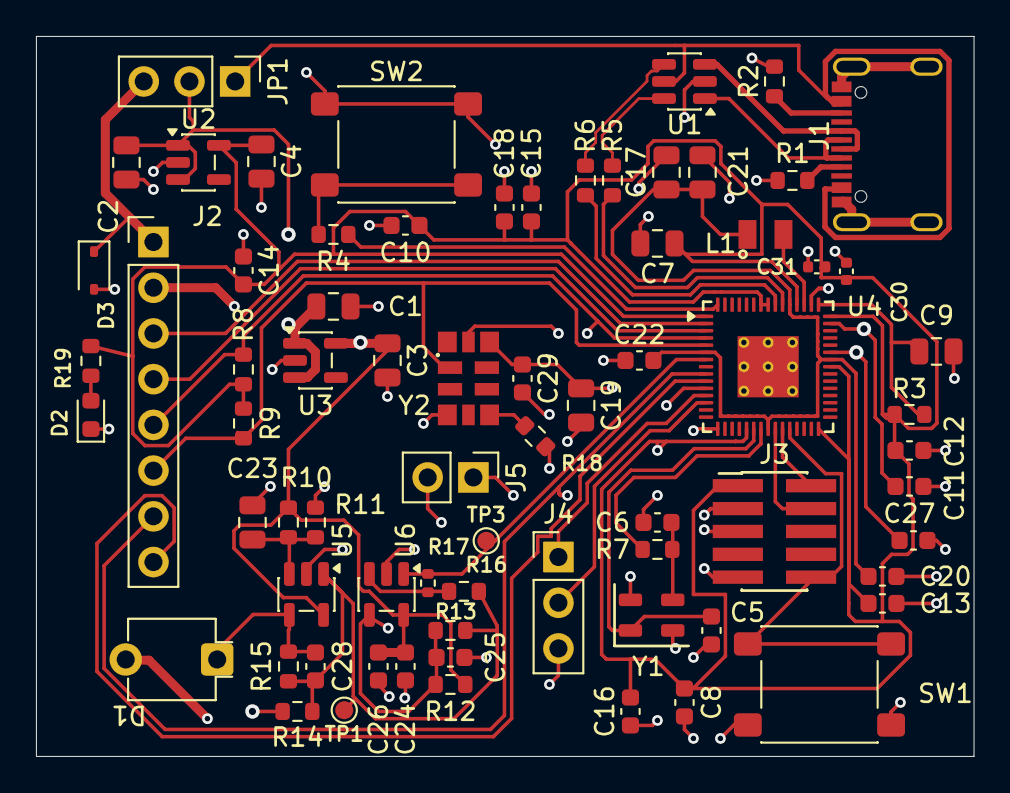
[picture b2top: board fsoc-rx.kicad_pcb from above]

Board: 4 copper layers, 52.1 x 40.0 mm, 73 parts (1 on the bottom side), 43 nets.
